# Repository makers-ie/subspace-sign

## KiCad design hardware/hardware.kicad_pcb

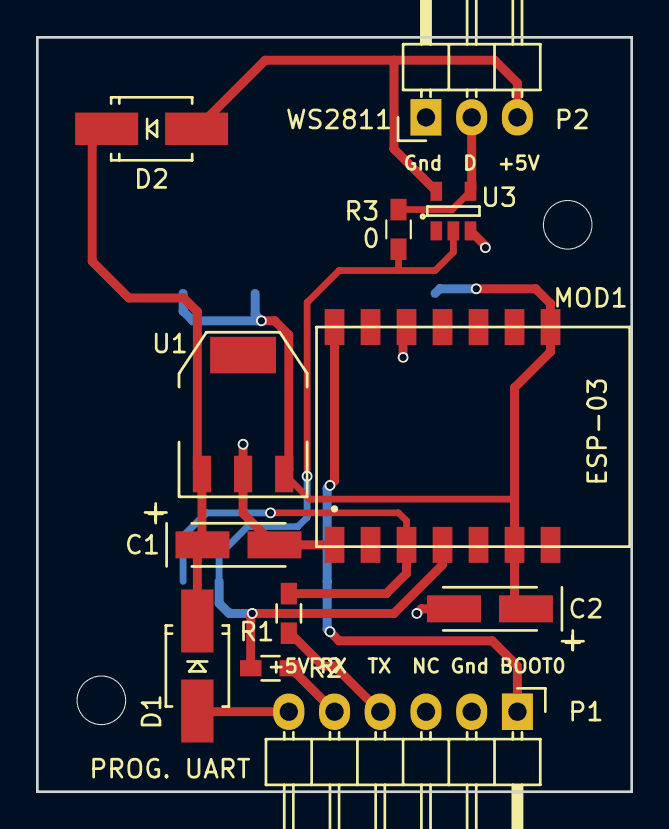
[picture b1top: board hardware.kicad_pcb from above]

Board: 2 copper layers, 33.0 x 41.9 mm, 13 parts (1 on the bottom side), 11 nets.

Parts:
C1, C2: CP; TantalC_SizeA_EIA-3216_HandSoldering
D1, D2: D_Schottky; SMA_Handsoldering
MOD1: ESP-03
MOD2: ESP-12F
P1: PROG. UART; Pin_Header_Angled_1x06
P2: WS2811; Pin_Header_Angled_1x03
R1, R2: 100; R_0603_HandSoldering
R3: 0; R_0603_HandSoldering
U1: MCP1754ST-3302E/MB; SOT-223
U3: SN74LV1T34; SOT-23-5

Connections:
+3V3: C2.1, MOD1.6, MOD1.8, MOD2.9, MOD2.11, MOD2.16, U1.3
+5V: C1.1, D1.1, D2.1, U1.1
GND: C1.2, C2.2, MOD1.1, MOD1.12, MOD2.1, MOD2.2, P1.2, P2.1, U1.2, U3.3
unnamed: D1.2, P1.6
unnamed: D2.2, P2.3, U3.5
unnamed: MOD1.3, MOD2.8, R1.1
unnamed: MOD1.4, MOD2.7, R2.1, R3.2, U3.2
unnamed: MOD1.14, MOD2.4, P1.1
unnamed: P1.4, R1.2
unnamed: P1.5, R2.2
unnamed: P2.2, R3.1, U3.4

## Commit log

2016-10-11 First version of hardware.
2016-10-11 Hardware manufacturing files v1.
2016-10-11 Initial version of the ws2811 library.
    This is just a running light with a single pixel running.
    The first LED is static at a bit pattern to test timings.
2016-11-19 Move ws2811_add_intr_ctx to cache.
2016-11-19 Insert final timing component values and fix a missing trace in PCB.
2016-11-19 Add a UART receiver that reboots on "q\n". Speeds up development.
2016-11-19 Add the WS2812B datasheet for future reference.
2017-05-27 Upgrade to PlatformIO 2.
2017-05-27 Update firmware and hardware to use I2S.
    No need for the multivibrators.
    Need resistor to avoid short with UART TX.
    Added resistor for easier bridging of U3.
2017-05-28 Add initial clock module using SNTP.
2017-05-28 Add some sparkle sprites around the minute hand.
2017-06-25 Add lwip and firebase WIP.

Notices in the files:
hardware/hardware.kicad_pcb:
© 2016 MAKERS-IE
